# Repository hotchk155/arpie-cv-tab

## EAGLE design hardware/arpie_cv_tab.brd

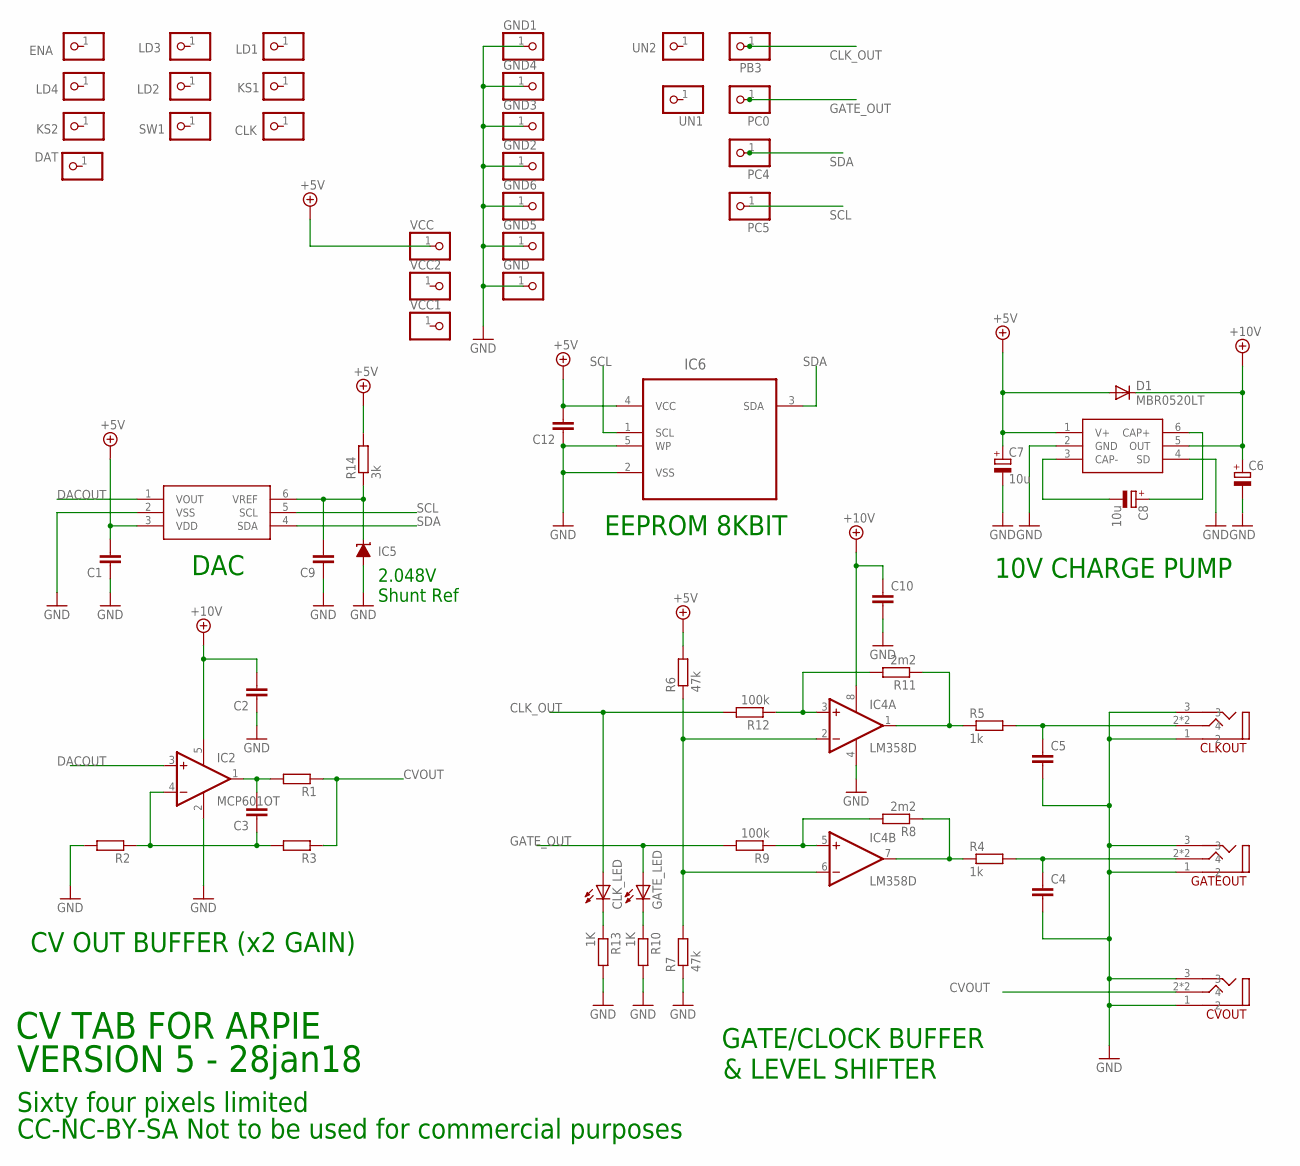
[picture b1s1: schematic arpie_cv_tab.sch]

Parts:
C1, C2, C3, C4, C5, C9, C10, C12: C-EUC0805; C0805
C6: CPOL-EUSMCA; SMC_A
C7, C8: 10u; SMC_A
CLK: PINHD-1X1; 1X01
CLKOUT: 3_5MM_PTH_MICRO
CLK_LED: LEDCHIP-LED0805; CHIP-LED0805
CVOUT: 3_5MM_PTH_MICRO
D1: MBR0520LT; SOD123
DAT: PINHD-1X1; 1X01
ENA: PINHD-1X1; 1X01
GATEOUT: 3_5MM_PTH_MICRO
GATE_LED: LEDCHIP-LED0805; CHIP-LED0805
GND, GND1, GND2, GND3, GND4, GND5, GND6: PINHD-1X1; 1X01
IC1: MCP4726; SOT23-6
IC2: MCP601OT; SOT23-5
IC3: LM27675M5_CHARGEPUMP; SOT23-6
IC4: LM358D; SO08
IC5: LM4041A12DBZ; DBZ_R-PDSO-G3
IC6: 24LC_16BT-I/OT; SOT95P290X145-5N
KS1, KS2: PINHD-1X1; 1X01
LD1, LD2, LD3, LD4: PINHD-1X1; 1X01
PB3: PINHD-1X1; 1X01
PC0, PC4, PC5: PINHD-1X1; 1X01
R1, R2, R3: R-EU_R0805; R0805
R4, R5: 1k; R0805
R6, R7: 47k; R0805
R8, R11: 2m2; R0805
R9, R12: 100k; R0805
R10, R13: 1K; R0805
R14: 3k; R0805
SW1: PINHD-1X1; 1X01
UN1, UN2: PINHD-1X1; 1X01
VCC, VCC1, VCC2: PINHD-1X1; 1X01

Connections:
+5V: C1.2, C7.+, C12.2, D1.A, IC1.3 (VDD), IC3.1 (V+), IC6.4 (VCC), R6.2, R14.2, VCC.1
+10V: C2.2, C6.+, C10.1, D1.C, IC2.5 (V+), IC3.5 (OUT), IC4.8 (V+)
CLK_OUT: CLK_LED.A, PB3.1, R12.2
CVOUT: CVOUT.2 (4), CVOUT.2A (4), R1.1, R3.1
DACOUT: IC1.1 (VOUT), IC2.3 (+IN)
GATE_OUT: GATE_LED.A, PC0.1, R9.2
GND: C1.1, C2.1, C4.2, C5.2, C6.-, C7.-, C9.1, C10.2, C12.1, CLKOUT.1 (2), CLKOUT.3, CVOUT.1 (2), CVOUT.3, GATEOUT.1 (2), GATEOUT.3, GND.1, GND1.1, GND2.1, GND3.1, GND4.1, GND5.1, GND6.1, IC1.2 (VSS), IC2.2 (V-), IC3.2 (GND), IC3.4 (SD), IC4.4 (V-), IC5.2 (A), IC6.2 (VSS), IC6.5 (WP), R2.2, R7.1, R10.2, R13.2
unnamed: IC4.2 (-IN), IC4.6 (-IN), R6.1, R7.2
unnamed: CLK_LED.C, R13.1
unnamed: GATE_LED.C, R10.1
unnamed: IC4.3 (+IN), R11.2, R12.1
unnamed: IC4.5 (+IN), R8.2, R9.1
unnamed: C9.2, IC1.6 (VREF), IC5.1 (C), R14.1
unnamed: IC4.1 (OUT), R5.1, R11.1
unnamed: C3.2, IC2.1 (OUT), R1.2
unnamed: IC4.7 (OUT), R4.1, R8.1
unnamed: C3.1, IC2.4 (-IN), R2.1, R3.2
unnamed: C5.1, CLKOUT.2 (4), CLKOUT.2A (4), R5.2
unnamed: C4.1, GATEOUT.2 (4), GATEOUT.2A (4), R4.2
unnamed: C8.+, IC3.6 (CAP+)
unnamed: C8.-, IC3.3 (CAP-)
SCL: IC1.5 (SCL), IC6.1 (SCL), PC5.1
SDA: IC1.4 (SDA), IC6.3 (SDA), PC4.1

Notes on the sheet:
10V CHARGE PUMP
DAC
CV OUT BUFFER (x2 GAIN)
GATE/CLOCK BUFFER
& LEVEL SHIFTER
CV TAB FOR ARPIE
VERSION 5 - 28jan18
Sixty four pixels limited
CC-NC-BY-SA Not to be used for commercial purposes
2.048V Shunt Ref
EEPROM 8KBIT

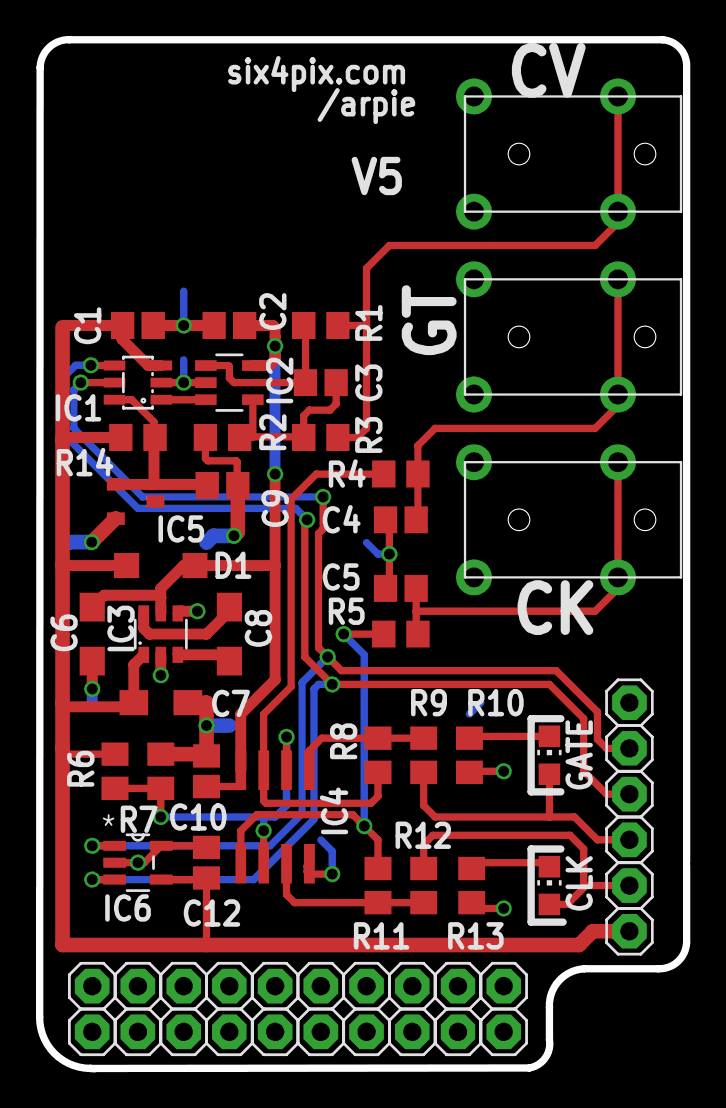
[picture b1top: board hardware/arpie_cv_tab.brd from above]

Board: 2 copper layers, 35.9 x 57.2 mm, 63 parts (0 on the bottom side), 23 nets.

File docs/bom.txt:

CVTAB V5 BILL OF MATERIALS 

C1		100n
C2		100n
C3		20p
C4		100n	
C5		100n	
C6		10u A-Case Tantalum
C7       	10u A-Case Tantalum               
C8       	10u A-Case Tantalum
C9		100n
C10		100n
C12		100n

D1       MBR0520LT

IC1      MCP4726
IC2      TSB611ILT
IC3      LM27675M5
IC4      LM358D
IC5      LM4040D20 2.048V
IC6      24AA64T-I/OT

R1		1k
R2		10k/0.1%
R3		10k/0.1%
R4		1k
R5		1k
R6       	47k
R7		47K
R8		2M2
R9       	100k
R10      	1K
R11		2M2
R12      	100k
R13      	1K
R14      	3k

CLK_LED 	0805 
GATE_LED        0805

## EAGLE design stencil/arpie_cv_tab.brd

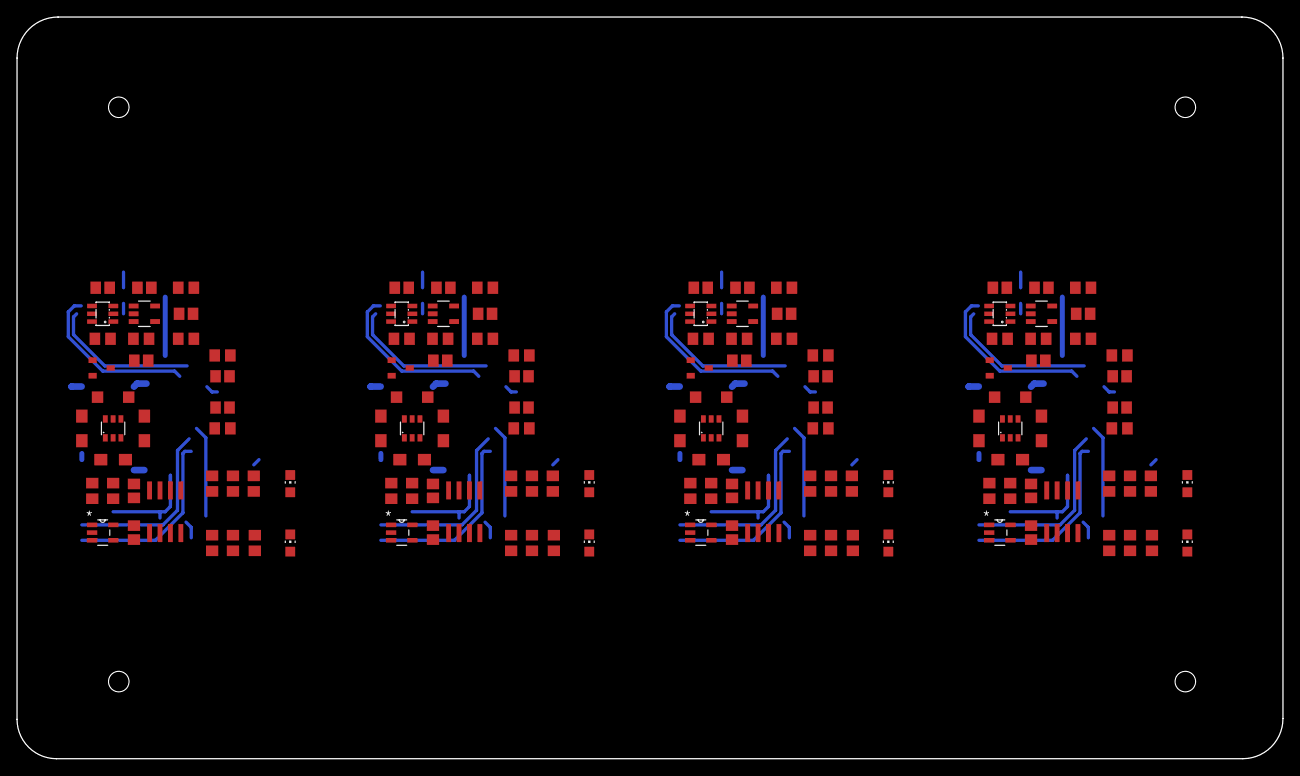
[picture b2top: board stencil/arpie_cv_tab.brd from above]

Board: 2 copper layers, 154.3 x 90.4 mm, 140 parts (0 on the bottom side), 92 nets.

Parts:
C1, C2, C3, C4, C5, C9, C10, C11, C12, C13, C14, C15, C16, C20, C21, C22, C23, C24, C25, C26, C27, C31, C32, C33, C34, C35, C36, C37, C38, C42, C43, C44: C0805
C6, C18, C29, C40: SMC_A
C7, C8, C17, C19, C28, C30, C39, C41: 10u; SMC_A
CLK_LED, CLK_LED1, CLK_LED2, CLK_LED3: CHIP-LED0805
D1, D2, D3, D4: MBR0520LT; SOD123
E$4, E$5, E$6, E$7: STENCILPIN
GATE_LED, GATE_LED1, GATE_LED2, GATE_LED3: CHIP-LED0805
IC1, IC7, IC13, IC19: MCP4726; SOT23-6
IC2, IC8, IC14, IC20: MCP601OT; SOT23-5
IC3, IC9, IC15, IC21: LM27675M5_CHARGEPUMP; SOT23-6
IC4, IC10, IC16, IC22: LM358D; SO08
IC5, IC11, IC17, IC23: LM4041A12DBZ; DBZ_R-PDSO-G3
IC6, IC12, IC18, IC24: 24LC_16BT-I/OT; SOT95P290X145-5N
R1, R2, R3, R19, R20, R21, R33, R34, R35, R47, R48, R49: R0805
R4, R5, R17, R18, R31, R32, R45, R46: 1k; R0805
R6, R7, R22, R23, R36, R37, R50, R51: 47k; R0805
R8, R11, R26, R27, R40, R41, R54, R55: 2m2; R0805
R9, R12, R24, R25, R38, R39, R52, R53: 100k; R0805
R10, R13, R15, R16, R29, R30, R43, R44: 1K; R0805
R14, R28, R42, R56: 3k; R0805

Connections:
+5V: C1.2, C7.+, C12.2, D1.A, IC1.3, IC3.1, IC6.4, R6.2, R14.2
+5V1: C14.2, C19.+, C22.2, D2.A, IC7.3, IC9.1, IC12.4, R23.2, R28.2
+5V2: C25.2, C30.+, C33.2, D3.A, IC13.3, IC15.1, IC18.4, R37.2, R42.2
+5V3: C36.2, C41.+, C44.2, D4.A, IC19.3, IC21.1, IC24.4, R51.2, R56.2
+10V: C2.2, C6.+, C10.1, D1.C, IC2.5, IC3.5, IC4.8
+10V1: C15.2, C18.+, C20.1, D2.C, IC8.5, IC9.5, IC10.8
+10V2: C26.2, C29.+, C31.1, D3.C, IC14.5, IC15.5, IC16.8
+10V3: C37.2, C40.+, C42.1, D4.C, IC20.5, IC21.5, IC22.8
CLK_OUT: CLK_LED.A, R12.2
CLK_OUT1: CLK_LED1.A, R24.2
CLK_OUT2: CLK_LED2.A, R38.2
CLK_OUT3: CLK_LED3.A, R52.2
CVOUT: R1.1, R3.1
CVOUT1: R19.1, R20.1
CVOUT2: R33.1, R34.1
CVOUT3: R47.1, R48.1
DACOUT: IC1.1, IC2.3
DACOUT1: IC7.1, IC8.3
DACOUT2: IC13.1, IC14.3
DACOUT3: IC19.1, IC20.3
GATE_OUT: GATE_LED.A, R9.2
GATE_OUT1: GATE_LED1.A, R25.2
GATE_OUT2: GATE_LED2.A, R39.2
GATE_OUT3: GATE_LED3.A, R53.2
GND: C1.1, C2.1, C4.2, C5.2, C6.-, C7.-, C9.1, C10.2, C12.1, IC1.2, IC2.2, IC3.2, IC3.4, IC4.4, IC5.2, IC6.2, IC6.5, R2.2, R7.1, R10.2, R13.2
GND1: C11.2, C13.2, C14.1, C15.1, C18.-, C19.-, C20.2, C21.1, C22.1, IC7.2, IC8.2, IC9.2, IC9.4, IC10.4, IC11.2, IC12.2, IC12.5, R15.2, R16.2, R21.2, R22.1
GND2: C23.2, C24.2, C25.1, C26.1, C29.-, C30.-, C31.2, C32.1, C33.1, IC13.2, IC14.2, IC15.2, IC15.4, IC16.4, IC17.2, IC18.2, IC18.5, R29.2, R30.2, R35.2, R36.1
GND3: C34.2, C35.2, C36.1, C37.1, C40.-, C41.-, C42.2, C43.1, C44.1, IC19.2, IC20.2, IC21.2, IC21.4, IC22.4, IC23.2, IC24.2, IC24.5, R43.2, R44.2, R49.2, R50.1
unnamed: IC4.2, IC4.6, R6.1, R7.2
unnamed: CLK_LED.C, R13.1
unnamed: GATE_LED.C, R10.1
unnamed: IC4.3, R11.2, R12.1
unnamed: IC4.5, R8.2, R9.1
unnamed: C9.2, IC1.6, IC5.1, R14.1
unnamed: C11.1, R17.2
unnamed: C13.1, R18.2
unnamed: IC4.1, R5.1, R11.1
unnamed: IC10.7, R18.1, R26.1
unnamed: C3.2, IC2.1, R1.2
unnamed: IC4.7, R4.1, R8.1
unnamed: IC10.1, R17.1, R27.1
unnamed: C16.2, IC8.1, R19.2
unnamed: C3.1, IC2.4, R2.1, R3.2
unnamed: C16.1, IC8.4, R20.2, R21.1
unnamed: C17.+, IC9.6
unnamed: C17.-, IC9.3
unnamed: C5.1, R5.2
unnamed: C4.1, R4.2
unnamed: IC10.2, IC10.6, R22.2, R23.1
unnamed: CLK_LED1.C, R16.1
unnamed: GATE_LED1.C, R15.1
unnamed: IC10.3, R24.1, R27.2
unnamed: IC10.5, R25.1, R26.2
unnamed: C21.2, IC7.6, IC11.1, R28.1
unnamed: C23.1, R31.2
unnamed: C24.1, R32.2
unnamed: IC16.7, R32.1, R40.1
unnamed: IC16.1, R31.1, R41.1
unnamed: C27.2, IC14.1, R33.2
unnamed: C27.1, IC14.4, R34.2, R35.1
unnamed: C28.+, IC15.6
unnamed: C28.-, IC15.3
unnamed: IC16.2, IC16.6, R36.2, R37.1
unnamed: CLK_LED2.C, R30.1
unnamed: GATE_LED2.C, R29.1
unnamed: C8.+, IC3.6
unnamed: C8.-, IC3.3
unnamed: IC16.3, R38.1, R41.2
unnamed: IC16.5, R39.1, R40.2
unnamed: C32.2, IC13.6, IC17.1, R42.1
unnamed: C34.1, R45.2
unnamed: C35.1, R46.2
unnamed: IC22.7, R46.1, R54.1
unnamed: IC22.1, R45.1, R55.1
unnamed: C38.2, IC20.1, R47.2
unnamed: C38.1, IC20.4, R48.2, R49.1
unnamed: C39.+, IC21.6
unnamed: C39.-, IC21.3
unnamed: IC22.2, IC22.6, R50.2, R51.1
unnamed: CLK_LED3.C, R44.1
unnamed: GATE_LED3.C, R43.1
unnamed: IC22.3, R52.1, R55.2
unnamed: IC22.5, R53.1, R54.2
unnamed: C43.2, IC19.6, IC23.1, R56.1
SCL: IC1.5, IC6.1
SCL1: IC7.5, IC12.1
SCL2: IC13.5, IC18.1
SCL3: IC19.5, IC24.1
SDA: IC1.4, IC6.3
SDA1: IC7.4, IC12.3
SDA2: IC13.4, IC18.3
SDA3: IC19.4, IC24.3

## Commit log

2015-05-29 :confetti_ball: Added .gitattributes & .gitignore files
2015-05-29 pcb ready
2018-11-17 v2 board
2018-12-02 v3 board
    add voltage reference
2018-12-06 reorg
2018-12-18 v5 added eeprom
2019-01-11 change jack outline
2019-01-26 add values to schematic
2019-01-28 V5 - change type of 3.5mm socket
2019-02-20 panel
2019-02-28 c4/c5=10n
2019-03-05 cal tool
2019-03-17 asdad
2019-03-17 BASE LINE
2019-03-18 hggj
2019-11-06 Add packing slip
2021-06-24 test rig updates
